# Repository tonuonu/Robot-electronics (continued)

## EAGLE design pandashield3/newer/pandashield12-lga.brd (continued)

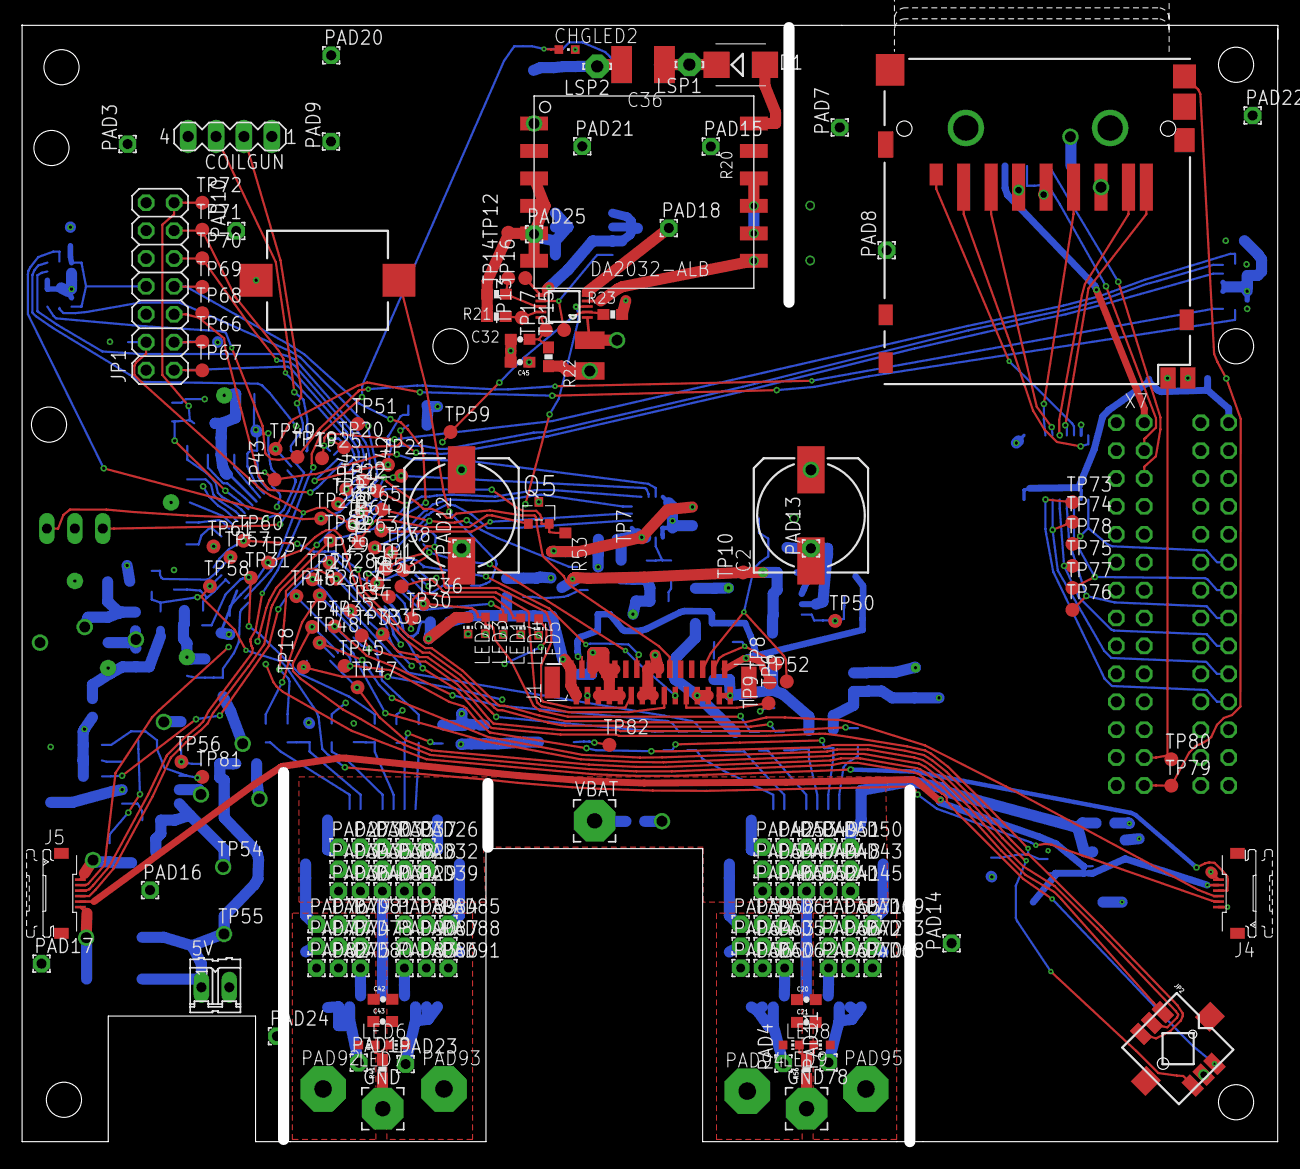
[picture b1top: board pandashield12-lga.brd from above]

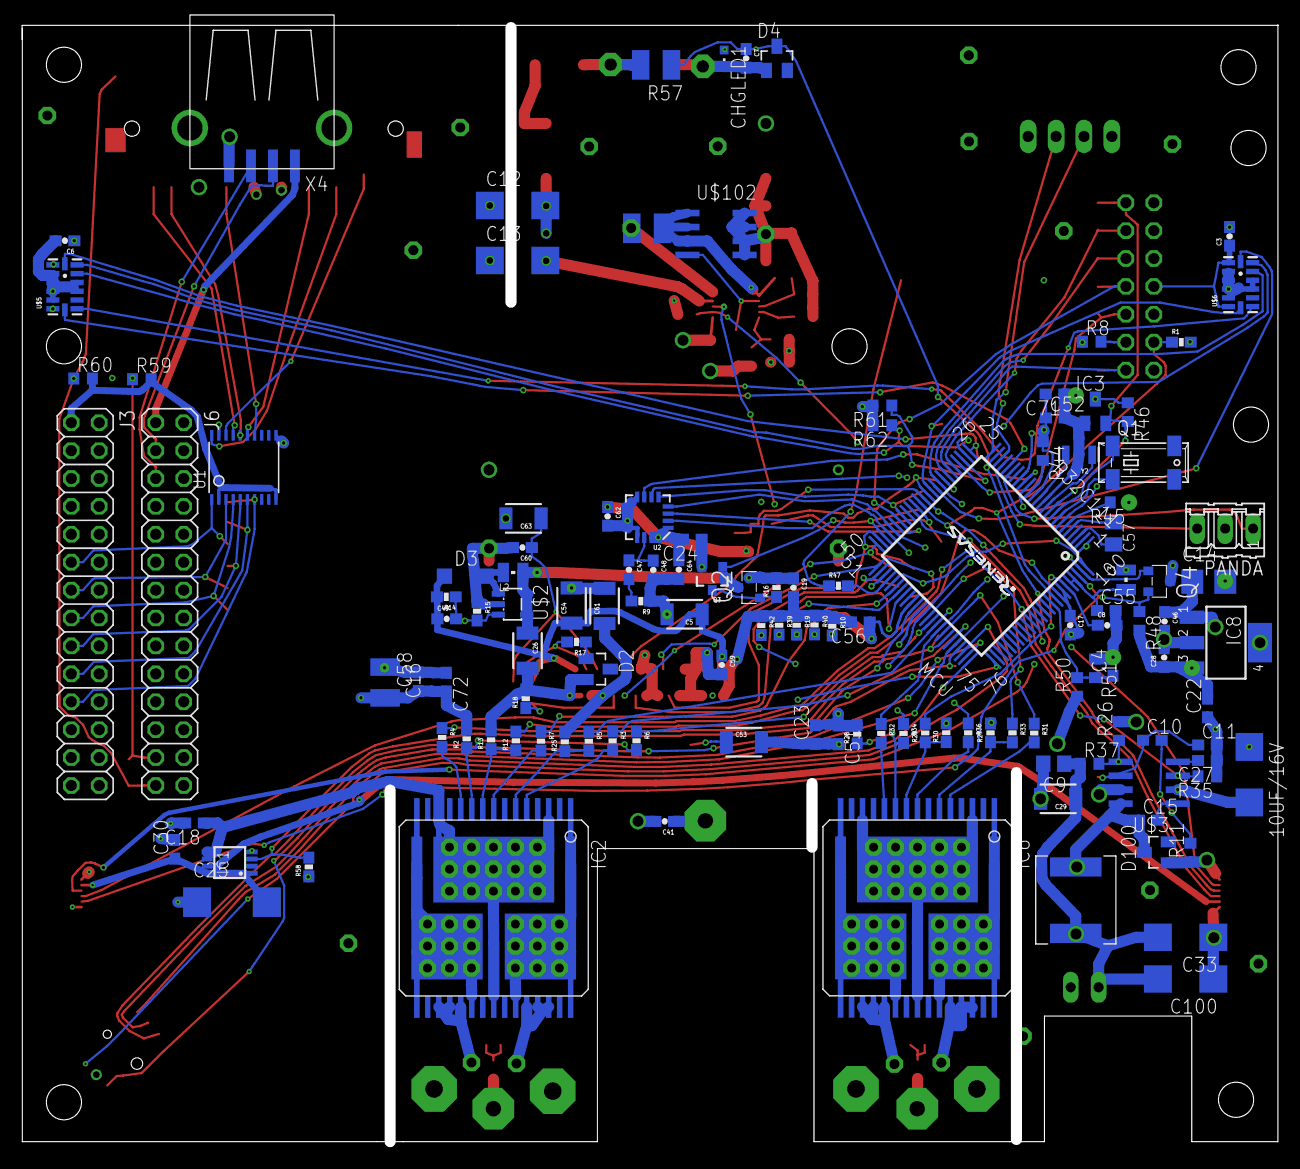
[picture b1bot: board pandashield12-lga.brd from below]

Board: 4 copper layers, 113.3 x 101.4 mm, 347 parts (129 on the bottom side), 148 nets.

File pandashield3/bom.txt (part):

Partlist exported from E:/pandashield3/pandashield12-lga.sch at 2012/05/13 18:20:45

Assembly variant: 

Qty Value                                           Device                Parts                                                                                                                                                                                                                                                                                                                                                                                                                                                                       
21                                                  1,6/0,9               PAD3, PAD4, PAD7, PAD8, PAD9, PAD10, PAD11, PAD12, PAD13, PAD14, PAD15, PAD16, PAD17, PAD18, PAD19, PAD20, PAD21, PAD22, PAD23, PAD24, PAD25                                                                                                                                                                                                                                                                                                                                
7                                                   3,81/1,4              GND, GND78, PAD1, PAD2, PAD5, PAD6, VBAT                                                                                                                                                                                                                                                                                                                                                                                                                                    
1                                                   CPOL-EUC/6032-28R     10UF/16V                                                                                                                                                                                                                                                                                                                                                                                                                                                                    
1                                                   CRYSTALMM20SS         Q1                                                                                                                                                                                                                                                                                                                                                                                                                                                                          
9                                                   LEDCHIP-LED0603       LED1, LED2, LED3, LED4, LED5, LED6, LED7, LED8, LED9                                                                                                                                                                                                                                                                                                                                                                                                                        
2                                                   LEDCHIPLED_0603       CHGLED1, CHGLED2                                                                                                                                                                                                                                                                                                                                                                                                                                                            
1                                                   M02                   5V                                                                                                                                                                                                                                                                                                                                                                                                                                                                          
1                                                   MA03                  PANDA                                                                                                                                                                                                                                                                                                                                                                                                                                                                       
1                                                   MA04-1                COILGUN                                                                                                                                                                                                                                                                                                                                                                                                                                                                     
1                                                   PINHD-2X7             JP1                                                                                                                                                                                                                                                                                                                                                                                                                                                                         
2                                                   PINHD-2X14            J3, J6                                                                                                                                                                                                                                                                                                                                                                                                                                                                      
1                                                   TRANSISTOR_NPNSOT23-3 Q3                                                                                                                                                                                                                                                                                                                                                                                                                                                                          
9   0,1                                             C-EUC0603             C22, C23, C51, C52, C55, C56, C58, C71, C72                                                                                                                                                                                                                                                                                                                                                                                                                                 
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
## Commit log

2011-08-09 Proto board for PSP LCD
2011-08-09 added pandashield schematics. Not usable yet!
2011-08-12 new changes commit
2011-08-15 Sensors board added
2011-08-15 LBR added with useful elements
2012-05-13 Mid-May final version commit.
2012-05-15 New, 4 layer gerbers generated
2012-07-07 new version in
2012-07-08 new version of board
2012-07-28 Garbage removal
2012-10-14 some new components added
2012-11-06 New components added
2013-08-11 new parts added to library
